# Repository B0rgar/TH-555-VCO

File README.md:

Thomas henry 555 vco with panel.
based on Eagleproject from Gerbster.nl. 

imported to kicad.
IO board redesigned for thonkicons jacks and wider spacing.
coarse pot replaced with 8 way octave switch,  smd resistors and tl431 underneath the rotary switch.
panel made.

PCBS ordered from JLCPCB.
will update after building and testing.
Looking at how the soldermask layer is overlapping the silkscreen on the pics from JLC,
I suspect I made a mistake and somehow didnt save the edited version of the panel.
time will tell.

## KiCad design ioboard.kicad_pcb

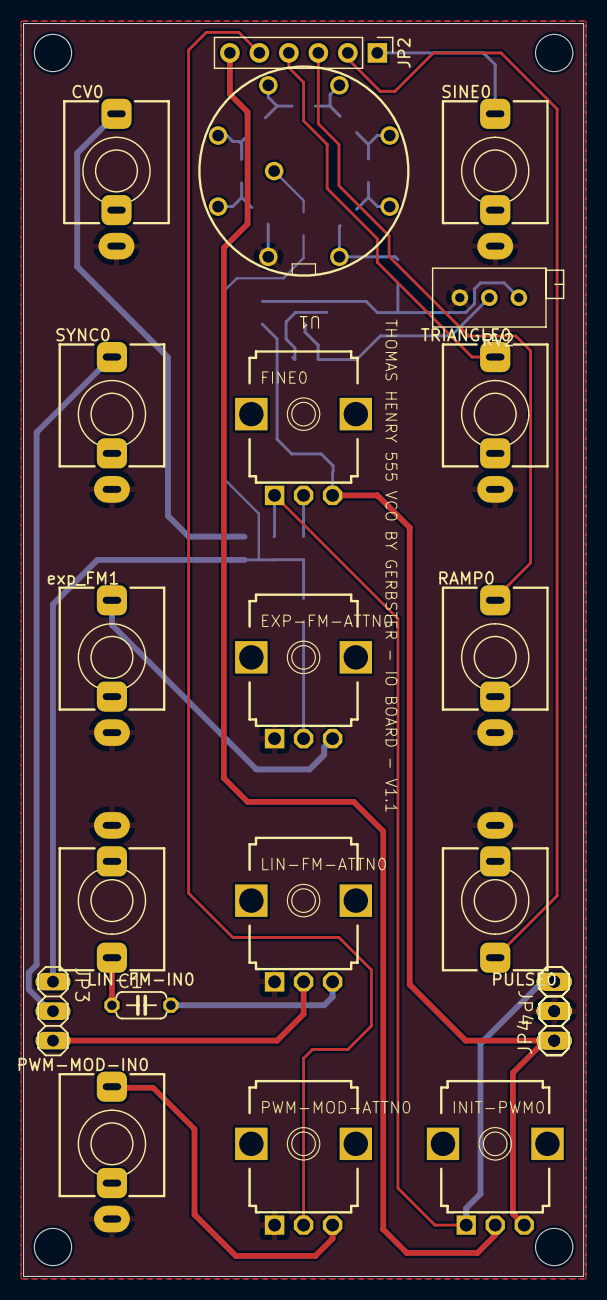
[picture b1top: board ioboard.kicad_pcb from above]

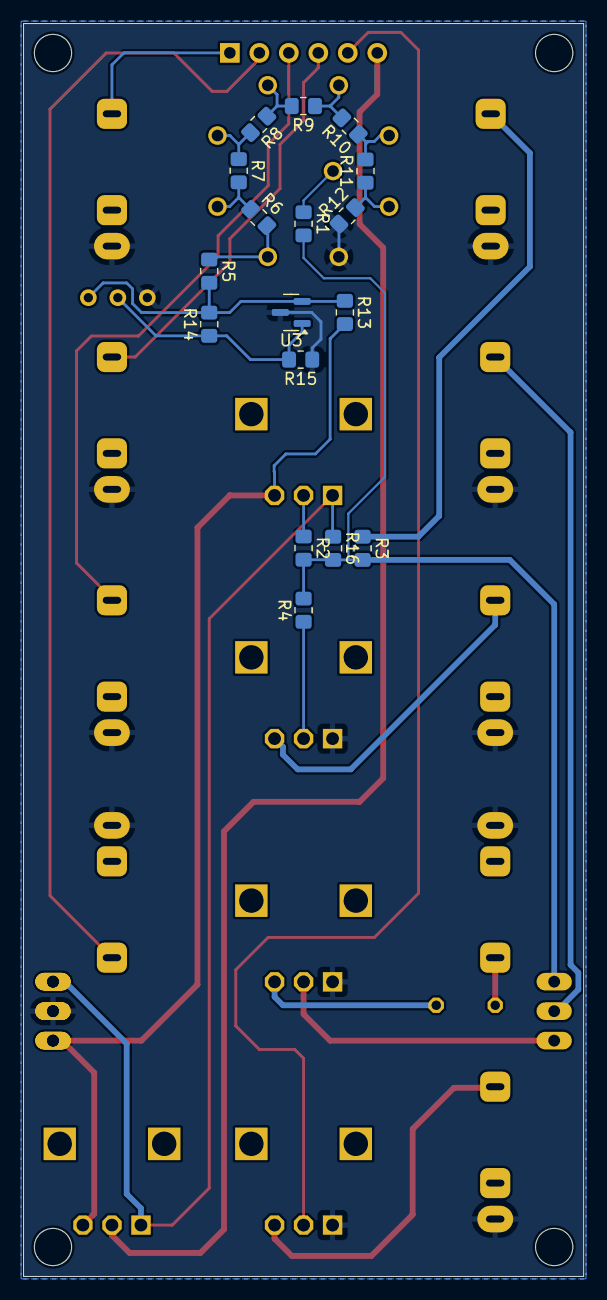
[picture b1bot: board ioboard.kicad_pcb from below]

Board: 2 copper layers, 48.3 x 108.0 mm, 42 parts (17 on the bottom side), 29 nets.

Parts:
@HOLE0, @HOLE1, @HOLE2, @HOLE3: (no value)
C1: .22uf; C050-024X044
CV0: PJ301BMPJ301BM; Jack_3.5mm_QingPu_WQP-PJ398SM_Vertical
EXP-FM-ATTN0: 100k; EVUF
FINE0: 100k; EVUF
INIT-PWM0: 100k; EVUF
JP2: PINHD-1X6; PinHeader_1x06_P2.54mm_Vertical
JP3, JP4: PINHD-1X3; 1X03
JP4#2: 1X03
LIN-FM-ATTN0: 100k; EVUF
LIN-FM-IN0: PJ301BMPJ301BM; Jack_3.5mm_QingPu_WQP-PJ398SM_Vertical
PULSE0: PJ301BMPJ301BM; Jack_3.5mm_QingPu_WQP-PJ398SM_Vertical
PWM-MOD-ATTN0: 100k; EVUF
PWM-MOD-IN0: PJ301BMPJ301BM; Jack_3.5mm_QingPu_WQP-PJ398SM_Vertical
R1, R3, R4: 100k; R_0805_2012Metric_Pad1.20x1.40mm_HandSolder
R2: 2.2M; R_0805_2012Metric_Pad1.20x1.40mm_HandSolder
R5, R6, R7, R8, R9, R10, R11, R12: 1k; R_0805_2012Metric_Pad1.20x1.40mm_HandSolder
R13: 1k2; R_0805_2012Metric_Pad1.20x1.40mm_HandSolder
R14, R15: DNP; R_0805_2012Metric_Pad1.20x1.40mm_HandSolder
R16: 330k; R_0805_2012Metric_Pad1.20x1.40mm_HandSolder
RAMP0: PJ301BMPJ301BM; Jack_3.5mm_QingPu_WQP-PJ398SM_Vertical
RV2: R_10k_Trim; Potentiometer_Bourns_3296X_Horizontal
SINE0: PJ301BMPJ301BM; Jack_3.5mm_QingPu_WQP-PJ398SM_Vertical
SYNC0: PJ301BMPJ301BM; Jack_3.5mm_QingPu_WQP-PJ398SM_Vertical
TRIANGLE0: PJ301BMPJ301BM; Jack_3.5mm_QingPu_WQP-PJ398SM_Vertical
U1: RS16_8PST_Rotary_Switch
U3: TL431DBZ; SOT-23
exp_FM1: PJ301BMPJ301BM; Jack_3.5mm_QingPu_WQP-PJ398SM_Vertical

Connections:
+12V: FINE0.3 (E), INIT-PWM0.3 (E), JP4.1, JP4#2.1, R13.2
-12V: FINE0.1 (A), INIT-PWM0.1 (A), JP4.3, JP4#2.3, R16.1
/HARD-SYNC: JP3.2, SYNC0.T
/LIN-FM: JP3.3, LIN-FM-ATTN0.2 (S)
/MULTI-IN: JP3.1, R1.2, R2.2, R3.2, R4.2, R16.2
/PULSE-OUT: JP2.2, PULSE0.T
/PULSE-WIDTH: INIT-PWM0.2 (S), JP2.6
/PWM-IN: JP2.5, PWM-MOD-ATTN0.2 (S)
/RAMP-OUT: JP2.3, RAMP0.T
/SINE-OUT: JP2.1, SINE0.T
/TRI-OUT: JP2.4, TRIANGLE0.T
GND: CV0.S, EXP-FM-ATTN0.1 (A), JP4.2, JP4#2.2, LIN-FM-ATTN0.1 (A), LIN-FM-IN0.S, PULSE0.S, PWM-MOD-ATTN0.1 (A), PWM-MOD-IN0.S, R12.1, R15.1, RAMP0.S, RV2.1, SINE0.S, SYNC0.S, TRIANGLE0.S, U1.1 (1_CCW), U3.3 (A), exp_FM1.S
unnamed: C1.1, LIN-FM-IN0.T
unnamed: CV0.T, R3.1
unnamed: EXP-FM-ATTN0.3 (E), exp_FM1.T
unnamed: EXP-FM-ATTN0.2 (S), R4.1
unnamed: FINE0.2 (S), R2.1
unnamed: C1.2, LIN-FM-ATTN0.3 (E)
unnamed: PWM-MOD-ATTN0.3 (E), PWM-MOD-IN0.T
unnamed: R6.1, R7.2, U1.7
unnamed: R7.1, R8.2, U1.6
unnamed: R8.1, R9.2, U1.5
unnamed: R10.1, R11.2, U1.3
unnamed: R9.1, R10.2, U1.4
unnamed: R11.1, R12.2, U1.2
unnamed: R5.1, R6.2, U1.8 (8_CW)
unnamed: R1.1, U1.9 (C)
unnamed: R5.2, R13.1, R14.2, RV2.3, U3.1 (K)
unnamed: R14.1, R15.2, RV2.2, U3.2 (REF)

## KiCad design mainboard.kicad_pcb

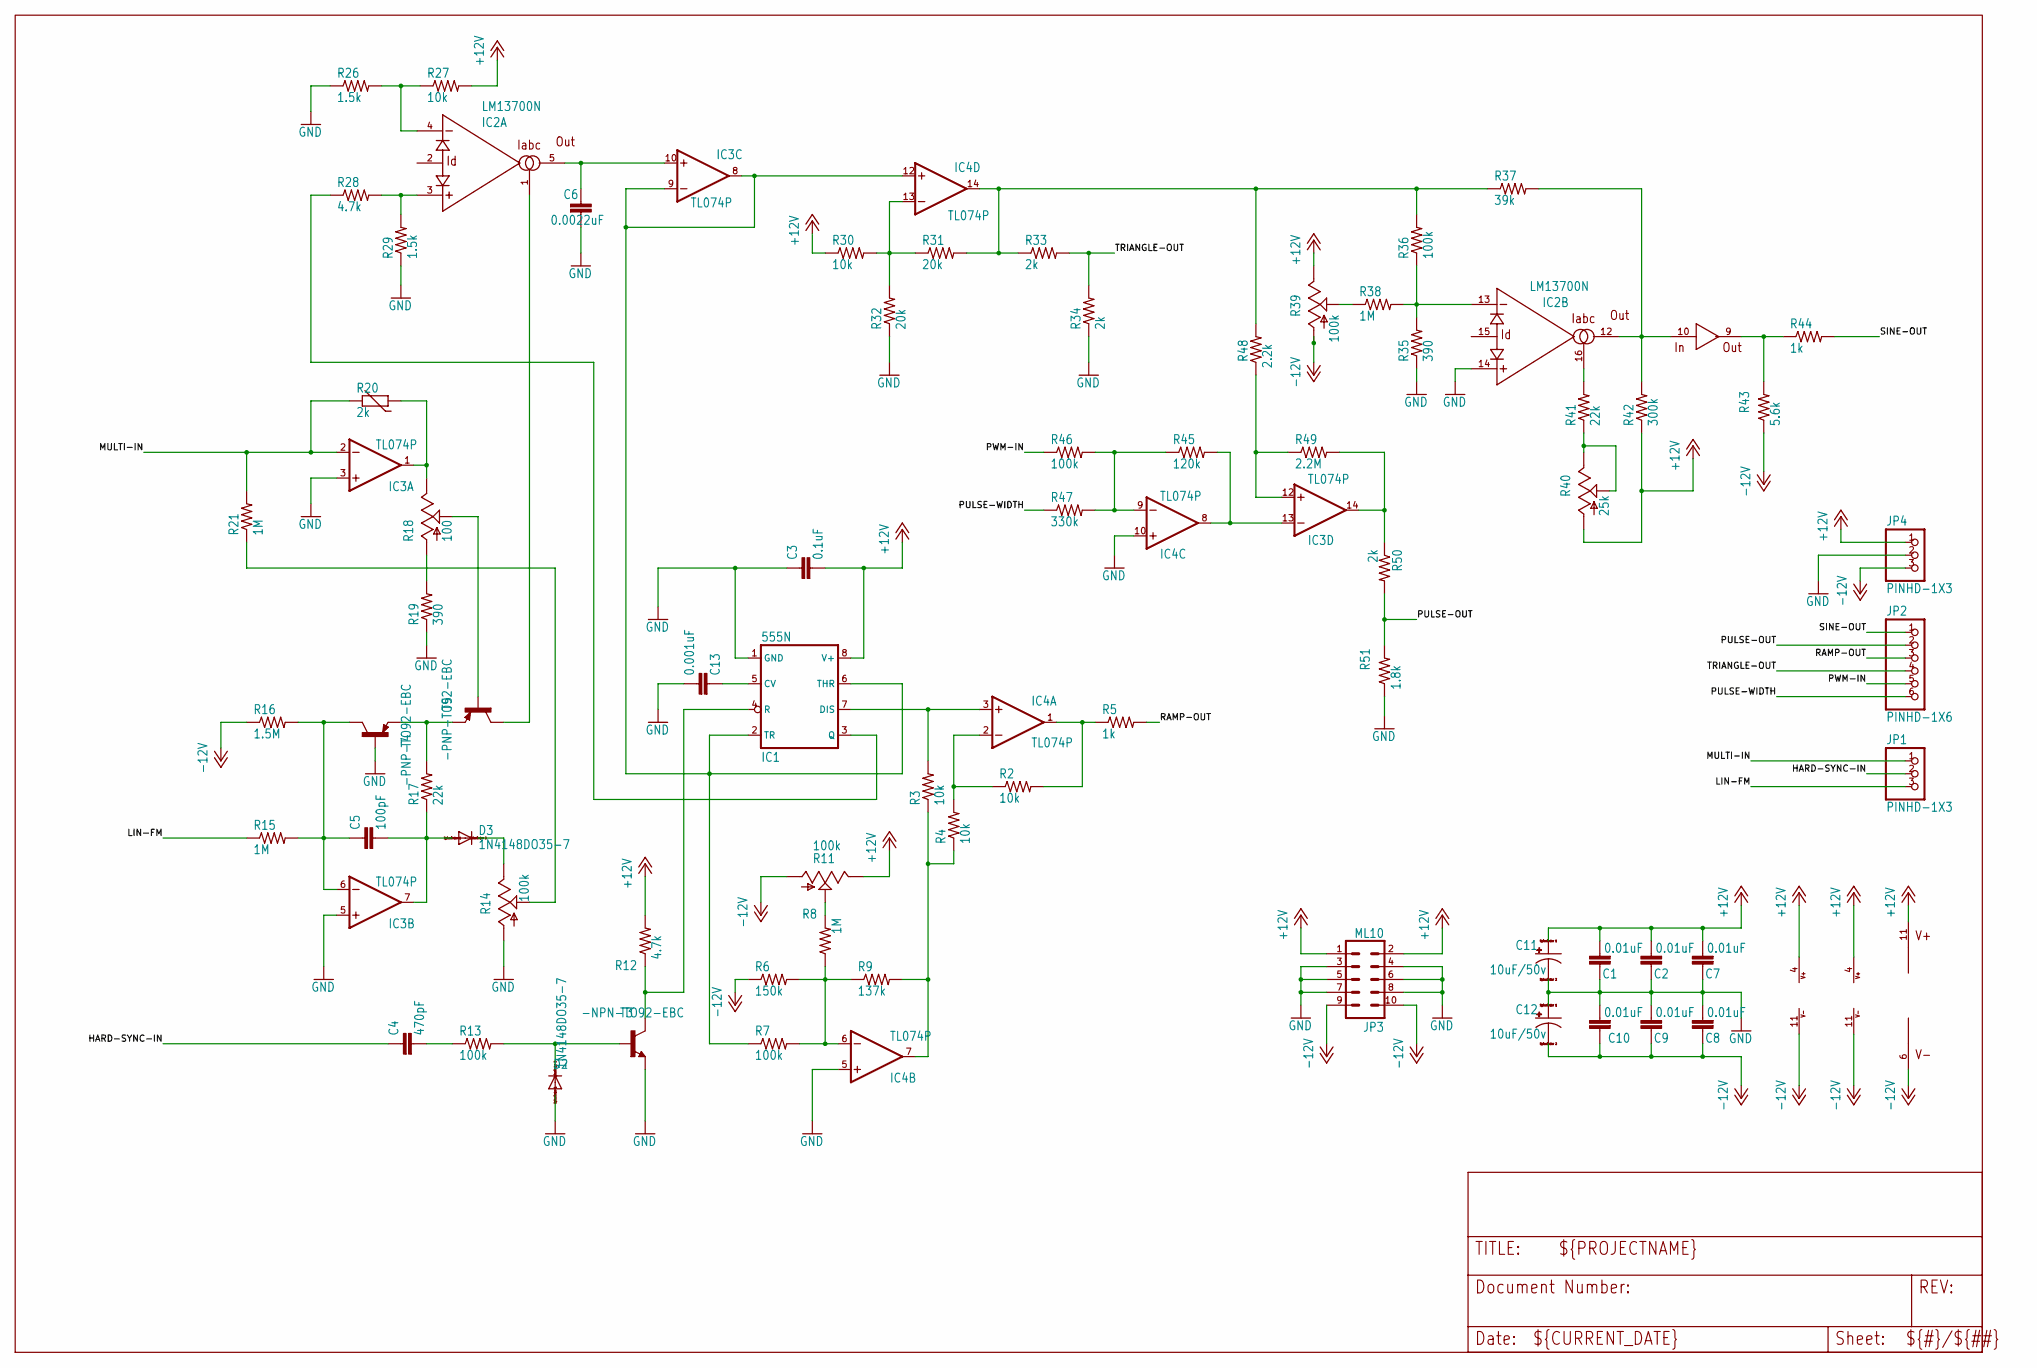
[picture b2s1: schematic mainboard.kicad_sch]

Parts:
C1, C2, C7, C8, C9, C10: 0.01uF; C050-024X044
C3: 0.1uF; C050-024X044
C4: 470pF; C050-024X044
C5: 100pF; C050-024X044
C6: 0.0022uF; C050-025X075
C11, C12: 10uF/50v; E2,5-6
C13: 0.001uF; C050-024X044
D2, D3: 1N4148DO35-7; DO35-7
IC1: 555N; DIL08
IC2: LM13700N; DIL16
IC3, IC4: TL074P; DIL14
JP1, JP4: PINHD-1X3; 1X03
JP2: PINHD-1X6; 1X06
JP3: ML10
R2, R3, R4, R27, R30: 10k; 0204_7
R5, R44: 1k; 0204_7
R6: 150k; 0204_7
R7, R13, R36, R46: 100k; 0204_7
R8, R15, R21, R38: 1M; 0204_7
R9: 137k; 0204_7
R11, R14, R39: 100k; RJ9W
R12, R28: 4.7k; 0204_7
R16: 1.5M; 0204_7
R17, R41: 22k; 0204_7
R18: 100; RJ9W
R19, R35: 390; 0204_7
R20: 2k; R-5
R26, R29: 1.5k; 0204_7
R31, R32: 20k; 0204_7
R33, R34, R50: 2k; 0204_7
R37: 39k; 0204_7
R40: 25k; RJ9W
R42: 300k; 0204_7
R43: 5.6k; 0204_7
R45: 120k; 0204_7
R47: 330k; 0204_7
R48: 2.2k; 0204_7
R49: 2.2M; 0204_7
R51: 1.8k; 0204_7
T3: -NPN-TO92-EBC; TO92-EBC
T4, T5: -PNP-TO92-EBC; TO92-EBC

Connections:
+12V: C1.2, C2.2, C3.2, C7.2, C11.+, IC1.8 (V+), IC2.11 (V+), IC3.4 (V+), IC4.4 (V+), JP3.1, JP3.2, JP4.1, R11.E, R12.2, R27.2, R30.1, R39.E, R40.A, R42.1
-12V: C8.1, C9.1, C10.1, C12.-, IC2.6 (V-), IC3.11 (V-), IC4.11 (V-), JP3.9, JP3.10, JP4.3, R6.1, R11.A, R16.1, R39.A, R43.1
GND: C1.1, C2.1, C3.1, C6.2, C7.1, C8.2, C9.2, C10.2, C11.-, C12.+, C13.1, D2.A, IC1.1 (GND), IC2.14 (+IN), IC3.3 (+IN), IC3.5 (+IN), IC4.5 (+IN), IC4.10 (+IN), JP3.3, JP3.4, JP3.5, JP3.6, JP3.7, JP3.8, JP4.2, R14.A, R19.1, R26.1, R29.1, R32.1, R34.1, R35.1, R51.1, T3.E, T4.B
HARD-SYNC-IN: C4.1, JP1.2
LIN-FM: JP1.3, R15.1
MULTI-IN: IC3.2 (-IN), JP1.1, R20.2, R21.2
unnamed: IC1.7 (DIS), IC4.3 (+IN), R3.2
unnamed: IC4.2 (-IN), R2.1, R4.2
unnamed: IC4.1 (OUT), R2.2, R5.1
unnamed: IC4.7 (OUT), R3.1, R4.1, R9.2
unnamed: IC4.6 (-IN), R6.2, R7.2, R8.1, R9.1
unnamed: R38.1, R39.S
unnamed: C5.1, IC3.6 (-IN), R15.2, R16.2, T4.C
unnamed: R8.2, R11.S
unnamed: C5.2, D3.A, IC3.7 (OUT), R17.1
unnamed: C4.2, R13.1
unnamed: D2.C, R13.2, T3.B
unnamed: IC1.4 (R), R12.1, T3.C
unnamed: R17.2, T4.E, T5.E
unnamed: D3.C, R14.E
unnamed: R14.S, R21.1
unnamed: IC3.1 (OUT), R18.E, R20.1
unnamed: R18.S, T5.B
unnamed: IC2.1 (IABC), T5.C
unnamed: R18.A, R19.2
unnamed: IC2.3 (+IN), R28.2, R29.2
unnamed: IC1.3 (Q), R28.1
unnamed: IC2.4 (-IN), R26.2, R27.1
unnamed: C6.1, IC2.5 (OUT), IC3.10 (+IN)
unnamed: IC1.2 (TR), IC1.6 (THR), IC3.8 (OUT), IC3.9 (-IN), IC4.12 (+IN), R7.1
unnamed: IC4.13 (-IN), R30.2, R31.1, R32.2
unnamed: IC2.13 (-IN), R35.2, R36.1, R38.2
unnamed: IC4.14 (OUT), R31.2, R33.1, R36.2, R37.1, R48.2
unnamed: IC2.16 (IABC), R41.2
unnamed: R40.E, R40.S, R41.1
unnamed: IC2.10 (IN), IC2.12 (OUT), R37.2, R42.2
unnamed: IC2.9 (OUT), R43.2, R44.1
unnamed: IC3.13 (-IN), IC4.8 (OUT), R45.2
unnamed: C13.2, IC1.5 (CV)
unnamed: IC4.9 (-IN), R45.1, R46.2, R47.2
unnamed: IC3.12 (+IN), R48.1, R49.1
unnamed: IC3.14 (OUT), R49.2, R50.1
PULSE-OUT: JP2.2, R50.2, R51.2
PULSE-WIDTH: JP2.6, R47.1
PWM-IN: JP2.5, R46.1
RAMP-OUT: JP2.3, R5.2
SINE-OUT: JP2.1, R44.2
TRIANGLE-OUT: JP2.4, R33.2, R34.2

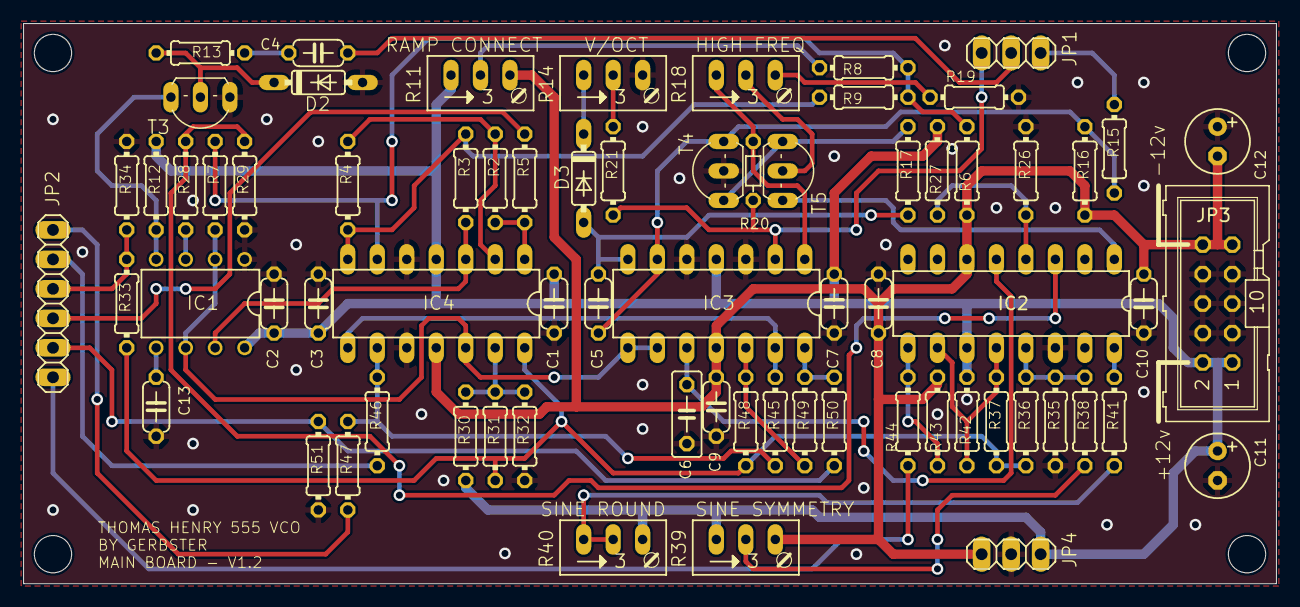
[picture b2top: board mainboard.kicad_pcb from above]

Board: 2 copper layers, 108.0 x 48.3 mm, 75 parts (0 on the bottom side), 48 nets.

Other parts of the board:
@HOLE0, @HOLE1, @HOLE2, @HOLE3: (no value)

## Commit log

2025-03-16 pics
